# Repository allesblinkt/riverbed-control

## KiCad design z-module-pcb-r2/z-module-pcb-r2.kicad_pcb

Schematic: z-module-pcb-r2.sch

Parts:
C1: 50u; CP_Radial_D7.5mm_P2.50mm
C2, C3, C4, C6, C7: 100n; C_0805
C5, C8: 20p; C_0805
D1: D_Schottky; D_SMA
D2: VacSense; LED_0805
D3: Status; LED_0805
D4: 5V; LED_0805
D5: 24V; LED_0805
D6, D8: BAT_46W; D_SOD-123
D7: Vacuum; LED_0805
D9: Eject; LED_0805
D10, D11, D12, D13, D14, D15, D16, D17, D18, D19, D20, D21, D22, D23, D24, D25, D26, D27, D28, D29: LED; LED_Osram_LW_E67C_LongPads_Thermal
F1: Rihanna; R_1812
F2: Drake; R_1812
HOLE1: 1; MountingHole_3mm
HOLE2: 2; MountingHole_3mm
HOLE3: 3; MountingHole_3mm
HOLE4: 4; MountingHole_3mm
HOLE5, HOLE6, HOLE7, HOLE8, HOLE9, HOLE10, HOLE11, HOLE12: CONN_01X01; MountingHole_2.2mm_M2
HOLE13, HOLE14: CONN_01X01; MountingHole_2.5mm
MB1, MB2, MB3, MB4, MB5, MB6, MB7, MB8, MB9, MB10, MB11, MB12, MB13, MB14, MB15, MB16, MB17, MB18, MB19, MB20: CONN_01X01; Mousebites_5_5mm_0-5mm
P1: Power; Molex_Microfit3_Header_02x02_Straight_43045-0428
P2: X1; RJ45_8-Vertical
P3: X2; RJ45_8-Vertical
P4: ISP; Pin_Header_Straight_2x03_Pitch2.54mm
P5: Z; Molex_Spox_board_4pin
P6: Vacuum; Molex_Microfit3_Header_02x04_Straight_43045-0828
P7: E; Molex_Spox_board_4pin
P8: HomeZ; Molex_Spox_board_3pin
P9: HomeE; Molex_Spox_board_3pin
P10, P18: Light; 0-188275-4_SMD_12-pin_female
P11, P12, P13, P14: 24V; Molex_PicoBlade_53048-0210_02x1.25mm_Angled
P15: 1; Molex_PicoBlade_53047-0210_02x1.25mm_Straight
P16: 2; Molex_PicoBlade_53047-0210_02x1.25mm_Straight
P17: 3; Molex_PicoBlade_53047-0210_02x1.25mm_Straight
P19: 4; Molex_PicoBlade_53047-0210_02x1.25mm_Straight
P20: 5; Molex_PicoBlade_53047-0210_02x1.25mm_Straight
P21: 6; Molex_PicoBlade_53047-0210_02x1.25mm_Straight
Q1, Q2, Q3, Q4, Q5, Q6, Q7, Q8: TSM3404_GSD; SOT-23
R1, R3, R5, R7, R9, R11, R13, R15, R17: 1K; R_0805
R2, R4, R6, R8, R10, R12, R14, R16, R18: *; R_0805
R19, R24, R26, R28, R29, R30, R31, R32, R33: 1K5; R_0805
R20, R21: 300R; R_0805
R22, R25, R27: 2K0; R_0805
R23: 10K; R_0805
R34, R35, R36, R37, R38, R39, R40, R41: 3K3; R_1206
U1: 74HC14; SOIC-14_3.9x8.7mm_Pitch1.27mm
U2, U4, U6: TLP281-4; SOIC-16_3.9x9.9mm_Pitch1.27mm
U3: 7805SR; TO-220
U5: 74HC04; SOIC-14_3.9x8.7mm_Pitch1.27mm
U7: ATMEGA328-AU; TQFP-32_7x7mm_Pitch0.8mm
Y1: Crystal_GND24; Crystal_SMD_3225-4pin_3.2x2.5mm

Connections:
+5V: C2.2, C3.2, C6.2, C7.2, F1.1, P3.8, P4.2, P8.1, P9.1, R1.1, R3.1, R5.1, R7.1, R9.1, R11.1, R13.1, R15.1, R17.1, R21.1, R23.2, U1.14 (VCC), U5.14 (VCC), U7.4 (VCC), U7.6 (VCC), U7.18 (AVCC); also elsewhere on the board
+24V: C1.1, D1.1 (K), D6.1 (K), D7.2 (A), D8.1 (K), D9.2 (A), P6.1, P6.2, P6.3, P10.2, P10.4, P10.6, P10.8, P10.10, P10.12, R22.1, U3.1 (IN); also elsewhere on the board
+28V: P15.1, P16.1, P17.1, P18.2, P18.4, P18.6, P18.8, P18.10, P18.12, P19.1, P20.1, P21.1
/AxisDriver1/M_1A: P5.3; also elsewhere on the board
/AxisDriver1/M_1B: P5.4; also elsewhere on the board
/AxisDriver1/M_2A: P5.2; also elsewhere on the board
/AxisDriver1/M_2B: P5.1; also elsewhere on the board
/AxisDriver2/M_1A: P7.3; also elsewhere on the board
/AxisDriver2/M_1B: P7.4; also elsewhere on the board
/AxisDriver2/M_2A: P7.2; also elsewhere on the board
/AxisDriver2/M_2B: P7.1; also elsewhere on the board
/CONTROL_COMM: P3.4, U4.5, U4.7, U6.1
/E_COMM: P2.8, U2.7, U4.1, U4.3
/E_DIR: U1.4; also elsewhere on the board
/E_DIR_IN: P2.6, R10.1
/E_EN: U1.2; also elsewhere on the board
/E_EN_IN: P2.7, R12.1
/E_HOME_OUT: P3.6, P9.2
/E_STEP: U1.6; also elsewhere on the board
/E_STEP_IN: P2.5, R8.1
/LED_1: P10.1, Q8.3 (D)
/LED_2: P10.3, Q7.3 (D)
/LED_3: P10.5, Q6.3 (D)
/LED_4: P10.7, Q5.3 (D)
/LED_5: P10.9, Q4.3 (D)
/LED_6: P10.11, Q3.3 (D)
/LED_A_A: P11.1, R34.2
/LED_A_K: D14.1 (K), P11.2
/LED_BO_1: P15.2, P18.1
/LED_BO_2: P16.2, P18.3
/LED_BO_3: P17.2, P18.5
/LED_BO_4: P18.7, P19.2
/LED_BO_5: P18.9, P20.2
/LED_BO_6: P18.11, P21.2
/LED_B_A: P12.1, R36.2
/LED_B_K: D19.1 (K), P12.2
/LED_C_A: P13.1, R38.2
/LED_C_K: D24.1 (K), P13.2
/LED_D_A: P14.1, R40.2
/LED_D_K: D29.1 (K), P14.2
/LIGHT_CTRL: U5.6, U7.32 ((PCINT18/INT0)PD2)
/LIGHT_CTRL_IN: P3.3, R18.1
/MISO: P4.1, U7.16 ((PCINT4/MISO)PB4)
/MOSI: P4.4, Q4.1 (G), R29.2, U7.15 ((PCINT3/OC2A/MOSI)PB3)
/PWM_LED_1: Q8.1 (G), R33.1, U7.1 ((PCINT19/OC2B/INT1)PD3)
/PWM_LED_2: Q7.1 (G), R32.1, U7.9 ((PCINT21/OC0B/T1)PD5)
/PWM_LED_3: Q6.1 (G), R31.1, U7.13 ((PCINT1/OC1A)PB1)
/PWM_LED_4: Q5.1 (G), R30.1, U7.14 ((PCINT2/OC1B/~SS~)PB2)
/PWM_LED_6: Q3.1 (G), R28.2, U7.10 ((PCINT22/OC0A/AIN0)PD6)
/RST: C4.2, P4.5, R23.1, U7.29 ((PCINT14/~RESET~)PC6)
/SCK: P4.3, U7.17 ((PCINT5/SCK)PB5)
/STATUSLED_1: R20.1, U7.12 ((PCINT0/CLKO/ICP1)PB0)
/VAC_AUX_AUX: P6.8
/VAC_BLACK_SENSE: D2.2 (A), P6.7
/VAC_BROWN_VAC: D8.2 (A), P6.6, Q2.3 (D), R25.1
/VAC_EJECT: Q1.1 (G), R24.1, U5.4
/VAC_EJECT_IN: P3.2, R16.1
/VAC_ON_IN: P3.1, R14.1
/VAC_SENSE_OUT: P3.7, U6.12
/VAC_VAC: Q2.1 (G), R26.1, U5.2
/VAC_WHITE_EJECT: D6.2 (A), P6.5, Q1.3 (D), R27.1
/XTAL1: C5.1, U7.8 ((PCINT7/XTAL2/TOSC2)PB7), Y1.1
/XTAL2: C8.1, U7.7 ((PCINT6/XTAL1/TOSC1)PB6), Y1.3
/Z_COMM: P2.4, U2.1, U2.3, U2.5
/Z_DIR: U1.10; also elsewhere on the board
/Z_DIR_IN: P2.2, R4.1
/Z_EN: U1.8; also elsewhere on the board
/Z_EN_IN: P2.3, R6.1
/Z_HOME_OUT: P3.5, P8.2
/Z_STEP: U1.12; also elsewhere on the board
/Z_STEP_IN: P2.1, R2.1
GND: C1.2, C2.1, C3.1, C4.1, C5.2, C6.1, C7.1, C8.2, D3.1 (K), D4.1 (K), D5.1 (K), P1.2, P1.4, P2.9, P3.9, P4.6, P6.4, P8.3, P9.3, Q1.2 (S), Q2.2 (S), Q3.2 (S), Q4.2 (S), Q5.2 (S), Q6.2 (S), Q7.2 (S), Q8.2 (S), R24.2, R26.2, R28.1, R29.1, R30.2, R31.2, R32.2, R33.2, U1.7 (GND), U2.9, U2.11, U2.13, U2.15, U3.2 (GND), U4.9, U4.11, U4.13, U4.15, U5.7 (GND), U6.6, U6.11, U6.15, U7.3 (GND), U7.5 (GND), U7.21 (GND), Y1.2, Y1.4; also elsewhere on the board
unnamed: D1.2 (A), F2.1
unnamed: D2.1 (K), R19.1
unnamed: D3.2 (A), R20.2
unnamed: D4.2 (A), R21.2
unnamed: D5.2 (A), R22.2
unnamed: D7.1 (K), R25.2
unnamed: D9.1 (K), R27.2
unnamed: D10.1 (K), D11.2 (A)
unnamed: D10.2 (A), R35.1
unnamed: D11.1 (K), D12.2 (A)
unnamed: D12.1 (K), D13.2 (A)
unnamed: D13.1 (K), D14.2 (A)
unnamed: D15.1 (K), D16.2 (A)
unnamed: D15.2 (A), R37.1
unnamed: D16.1 (K), D17.2 (A)
unnamed: D17.1 (K), D18.2 (A)
unnamed: D18.1 (K), D19.2 (A)
unnamed: D20.1 (K), D21.2 (A)
unnamed: D20.2 (A), R39.1
unnamed: D21.1 (K), D22.2 (A)
unnamed: D22.1 (K), D23.2 (A)
unnamed: D23.1 (K), D24.2 (A)
unnamed: D25.1 (K), D26.2 (A)
unnamed: D25.2 (A), R41.1
unnamed: D26.1 (K), D27.2 (A)
unnamed: D27.1 (K), D28.2 (A)
unnamed: D28.1 (K), D29.2 (A)
unnamed: F1.2, U3.3 (OUT)
unnamed: F2.2, P1.1, P1.3
unnamed: R1.2, U1.13, U2.16
unnamed: R2.2, U2.2
unnamed: R3.2, U1.11, U2.14
unnamed: R4.2, U2.4
unnamed: R5.2, U1.9, U2.12
unnamed: R6.2, U2.6
unnamed: R7.2, U1.5, U2.10
unnamed: R8.2, U2.8
unnamed: R9.2, U1.3, U4.16
unnamed: R10.2, U4.2
unnamed: R11.2, U1.1, U4.14
unnamed: R12.2, U4.4
unnamed: R13.2, U4.12, U5.1
unnamed: R14.2, U4.6
unnamed: R15.2, U4.10, U5.3
unnamed: R16.2, U4.8
unnamed: R17.2, U5.5, U6.16
unnamed: R18.2, U6.2
unnamed: R19.2, U6.5
unnamed: R34.1, R35.2
unnamed: R36.1, R37.2
unnamed: R38.1, R39.2
unnamed: R40.1, R41.2

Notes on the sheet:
Power Input
Status LEDs
Power LEDs
Holes
Motor Drivers
Processor
Switch Inputs
5 V Reg
* = 270 R @ 5V

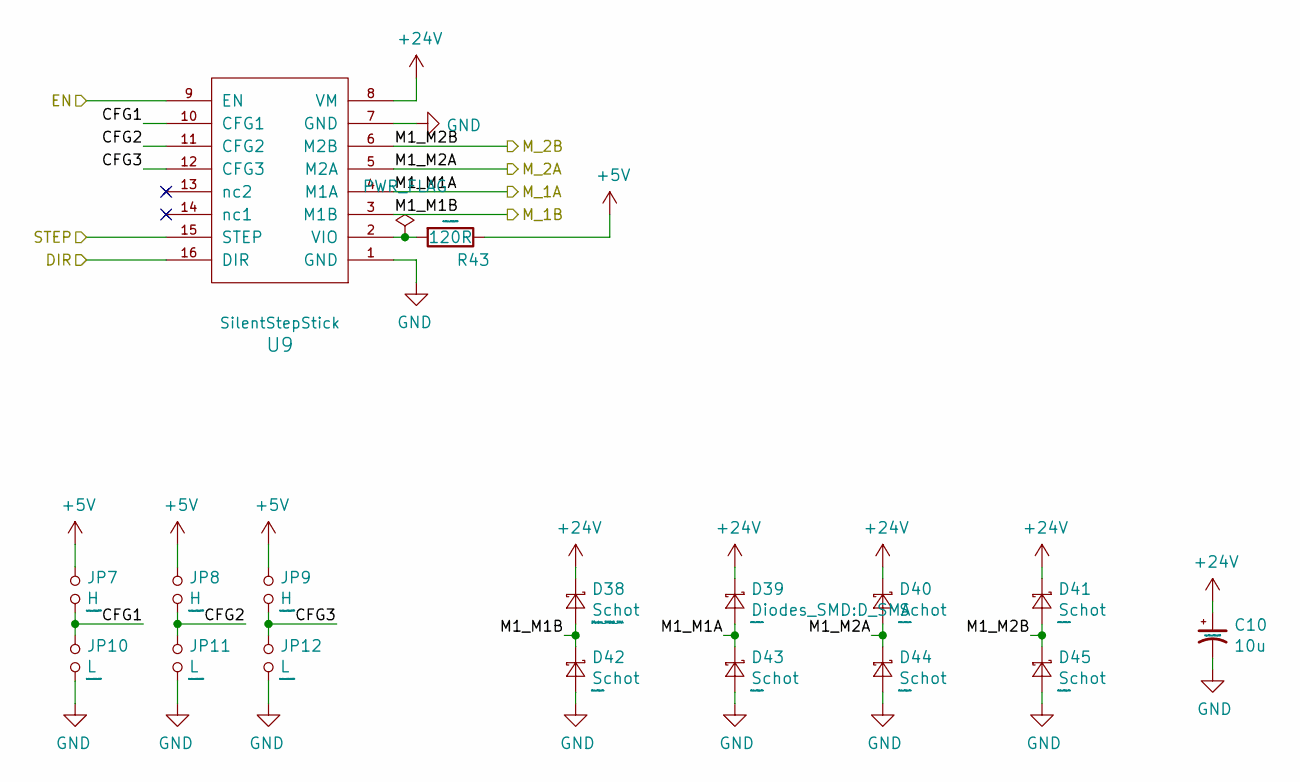
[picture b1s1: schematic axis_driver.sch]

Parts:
C9: 10u; C_1210
D30, D32, D33, D34, D35, D36, D37: Schot; D_SMA
D31: Diodes_SMD:D_SMA; D_SMA
JP1, JP2, JP3: H; R_0805
JP4, JP5, JP6: L; R_0805
R42: 120R; R_0805
U8: SilentStepStick

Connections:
+5V: JP1.1, JP2.1, JP3.1, R42.1; also elsewhere on the board
+24V: C9.1, D30.1 (K), D31.1 (K), D32.1 (K), D33.1 (K), U8.8 (VM); also elsewhere on the board
/AxisDriver2/CFG1: JP1.2, JP4.1, U8.10 (CFG1)
/AxisDriver2/CFG2: JP2.2, JP5.1, U8.11 (CFG2)
/AxisDriver2/CFG3: JP3.2, JP6.1, U8.12 (CFG3)
/AxisDriver2/M_1A: D31.2 (A), D35.1 (K), U8.4 (M1A); also elsewhere on the board
/AxisDriver2/M_1B: D30.2 (A), D34.1 (K), U8.3 (M1B); also elsewhere on the board
/AxisDriver2/M_2A: D32.2 (A), D36.1 (K), U8.5 (M2A); also elsewhere on the board
/AxisDriver2/M_2B: D33.2 (A), D37.1 (K), U8.6 (M2B); also elsewhere on the board
/E_DIR: U8.16 (DIR); also elsewhere on the board
/E_EN: U8.9 (EN); also elsewhere on the board
/E_STEP: U8.15 (STEP); also elsewhere on the board
GND: C9.2, D34.2 (A), D35.2 (A), D36.2 (A), D37.2 (A), JP4.2, JP5.2, JP6.2, U8.1 (GND), U8.7 (GND); also elsewhere on the board
unnamed: R42.2, U8.2 (VIO)

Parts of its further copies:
C10: 10u; C_1210
D38, D40, D41, D42, D43, D44, D45: Schot; D_SMA
D39: Diodes_SMD:D_SMA; D_SMA
JP7, JP8, JP9: H; R_0805
JP10, JP11, JP12: L; R_0805
R43: 120R; R_0805
U9: SilentStepStick

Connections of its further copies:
+5V: JP7.1, JP8.1, JP9.1, R43.1; also elsewhere on the board
+24V: C10.1, D38.1 (K), D39.1 (K), D40.1 (K), D41.1 (K), U9.8 (VM); also elsewhere on the board
/AxisDriver1/CFG1: JP7.2, JP10.1, U9.10 (CFG1)
/AxisDriver1/CFG2: JP8.2, JP11.1, U9.11 (CFG2)
/AxisDriver1/CFG3: JP9.2, JP12.1, U9.12 (CFG3)
/AxisDriver1/M_1A: D39.2 (A), D43.1 (K), U9.4 (M1A); also elsewhere on the board
/AxisDriver1/M_1B: D38.2 (A), D42.1 (K), U9.3 (M1B); also elsewhere on the board
/AxisDriver1/M_2A: D40.2 (A), D44.1 (K), U9.5 (M2A); also elsewhere on the board
/AxisDriver1/M_2B: D41.2 (A), D45.1 (K), U9.6 (M2B); also elsewhere on the board
/Z_DIR: U9.16 (DIR); also elsewhere on the board
/Z_EN: U9.9 (EN); also elsewhere on the board
/Z_STEP: U9.15 (STEP); also elsewhere on the board
GND: C10.2, D42.2 (A), D43.2 (A), D44.2 (A), D45.2 (A), JP10.2, JP11.2, JP12.2, U9.1 (GND), U9.7 (GND); also elsewhere on the board
unnamed: R43.2, U9.2 (VIO)

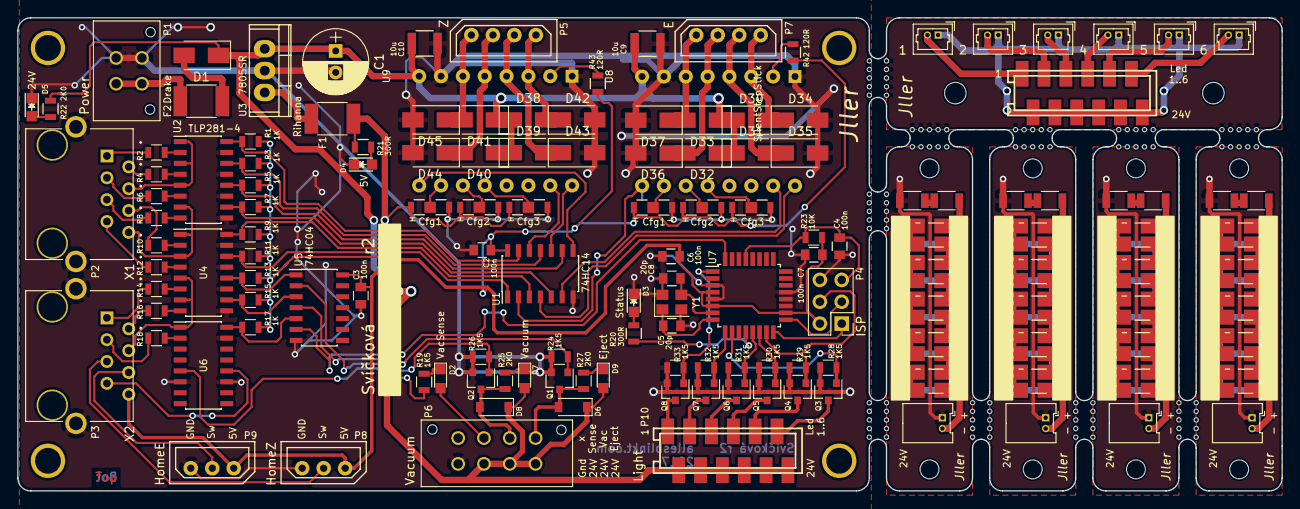
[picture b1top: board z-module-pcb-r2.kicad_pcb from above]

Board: 2 copper layers, 147.0 x 55.0 mm, 185 parts (0 on the bottom side), 131 nets.

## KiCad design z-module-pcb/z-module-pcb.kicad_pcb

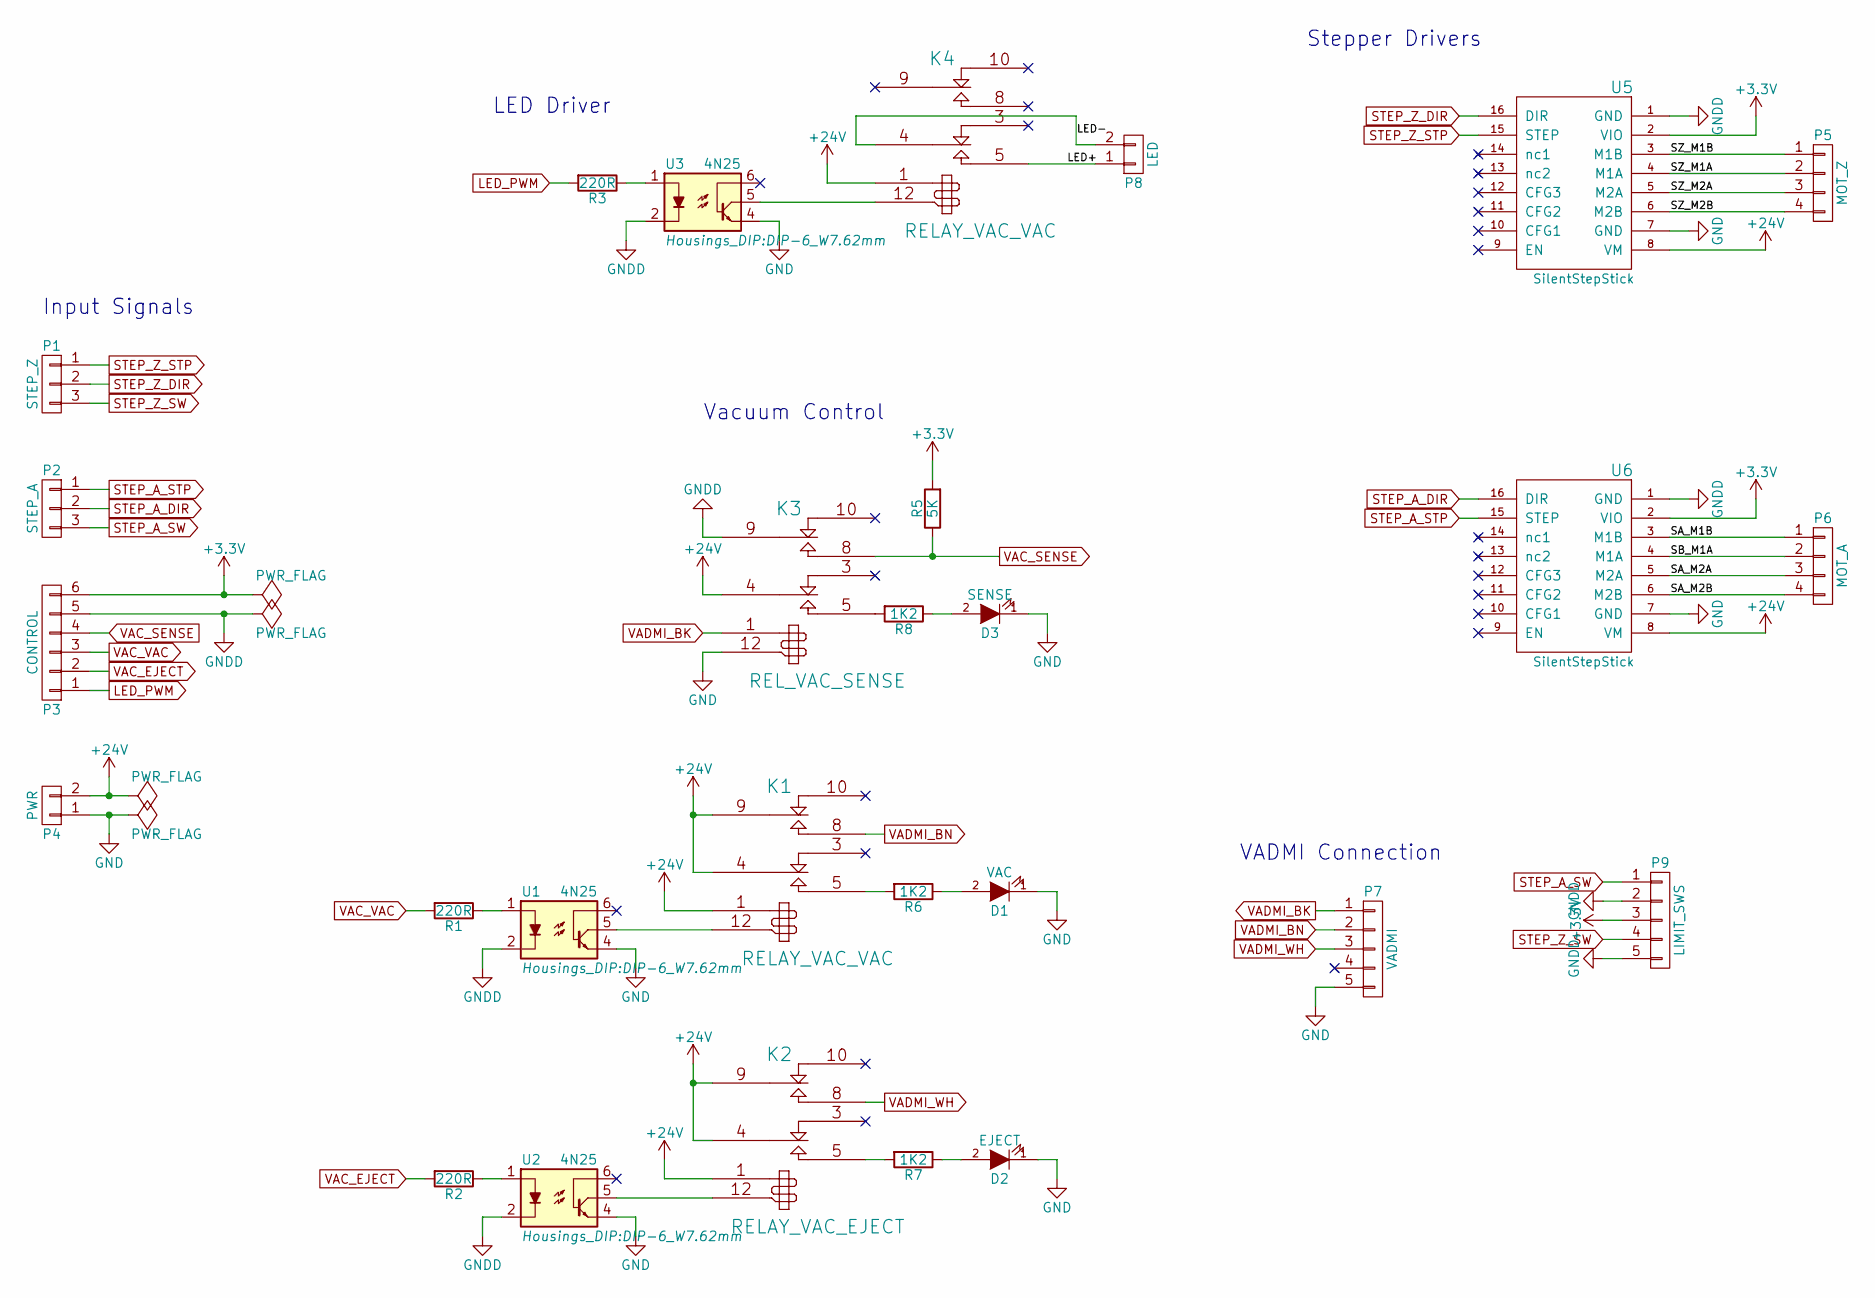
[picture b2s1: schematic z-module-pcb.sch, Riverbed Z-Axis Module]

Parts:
D1: VAC; LED-3MM
D2: EJECT; LED-3MM
D3: SENSE; LED-3MM
K1, K4: RELAY_VAC_VAC; AxicomRelay-V23079
K2: RELAY_VAC_EJECT; AxicomRelay-V23079
K3: REL_VAC_SENSE; AxicomRelay-V23079
P1: STEP_Z; AKL_182-03
P2: STEP_A; AKL_182-03
P3: CONTROL; AKL_182-06
P4: PWR; AKL_182-02
P5: MOT_Z; AKL_182-04
P6: MOT_A; AKL_182-04
P7: VADMI; AKL_182-05
P8: LED; AKL_182-02
P9: LIMIT_SWS; AKL_182-05
R1, R2, R3: 220R; Resistor_Horizontal_RM10mm
R5: 5K; Resistor_Horizontal_RM10mm
R6, R7, R8: 1K2; Resistor_Horizontal_RM10mm
U1, U2, U3: 4N25; DIP-6_W7.62mm
U5, U6: SilentStepStick

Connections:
+3V3: P3.6, P9.3, R5.2, U5.2 (VIO), U6.2 (VIO)
+24V: K1.1, K1.4, K1.9, K2.1, K2.4, K2.9, K3.4, K4.1, P4.2, U5.8 (VM), U6.8 (VM)
/LED+: K4.5, P8.1
/LED-: K4.4, P8.2
/SA_M1B: P6.1, U6.3 (M1B)
/SA_M2A: P6.3, U6.5 (M2A)
/SA_M2B: P6.4, U6.6 (M2B)
/SB_M1A: P6.2, U6.4 (M1A)
/SZ_M1A: P5.2, U5.4 (M1A)
/SZ_M1B: P5.1, U5.3 (M1B)
/SZ_M2A: P5.3, U5.5 (M2A)
/SZ_M2B: P5.4, U5.6 (M2B)
GND: D1.1 (K), D2.1 (K), D3.1 (K), K3.12, P4.1, P7.5, U1.4, U2.4, U3.4, U5.7 (GND), U6.7 (GND)
GNDD: K3.9, P3.5, P9.2, P9.5, U1.2, U2.2, U3.2, U5.1 (GND), U6.1 (GND)
LED_PWM: P3.1, R3.2
unnamed: D1.2 (A), R6.1
unnamed: D2.2 (A), R7.1
unnamed: D3.2 (A), R8.1
unnamed: K1.5, R6.2
unnamed: K1.12, U1.5
unnamed: K2.5, R7.2
unnamed: K2.12, U2.5
unnamed: K3.5, R8.2
unnamed: K4.12, U3.5
unnamed: R1.1, U1.1
unnamed: R2.1, U2.1
unnamed: R3.1, U3.1
STEP_A_DIR: P2.2, U6.16 (DIR)
STEP_A_STP: P2.1, U6.15 (STEP)
STEP_A_SW: P2.3, P9.1
STEP_Z_DIR: P1.2, U5.16 (DIR)
STEP_Z_STP: P1.1, U5.15 (STEP)
STEP_Z_SW: P1.3, P9.4
VAC_EJECT: P3.2, R2.2
VAC_SENSE: K3.8, P3.4, R5.1
VAC_VAC: P3.3, R1.2
VADMI_BK: K3.1, P7.1
VADMI_BN: K1.8, P7.2
VADMI_WH: K2.8, P7.3

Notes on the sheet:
Stepper Drivers
VADMI Connection
LED Driver
Vacuum Control
Input Signals

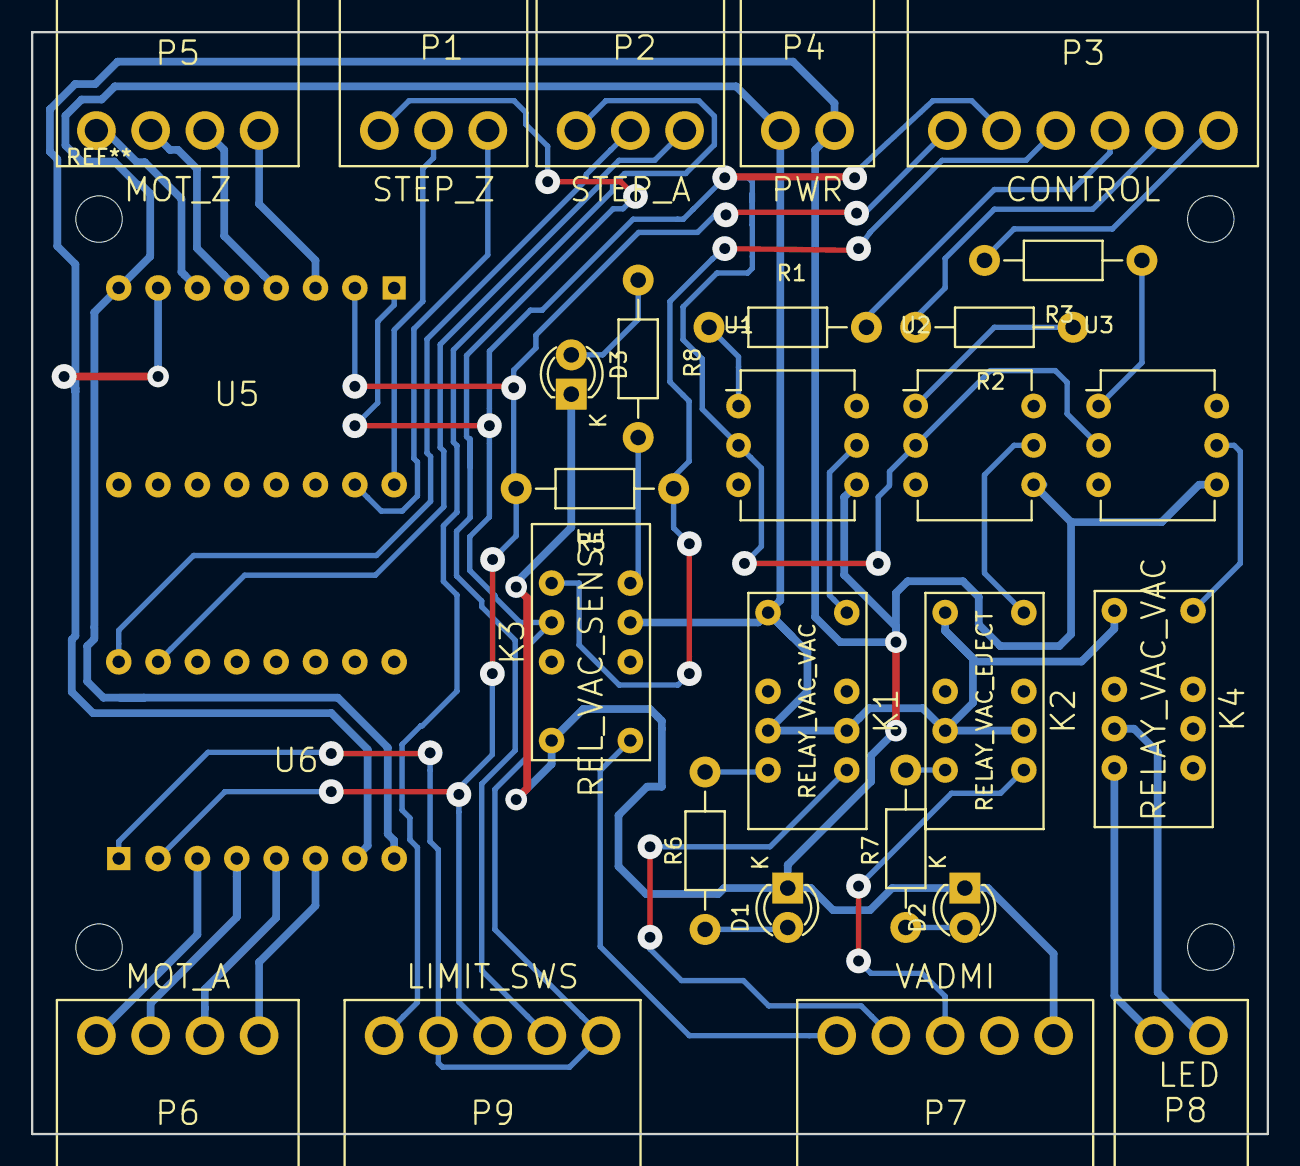
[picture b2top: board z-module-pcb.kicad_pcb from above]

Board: 2 copper layers, 79.8 x 71.1 mm, 28 parts (0 on the bottom side), 39 nets.

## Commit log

2015-11-08 Readme
2015-11-08 Added gitignore
2015-11-09 Added notes for signals of Z-Axis
2015-11-09 Relay thoughts
2015-11-09 Ignoring some Kicad files
2015-11-09 Signal definitions
2015-11-09 PCB schematic and layout WiP. Libraries with custom components.
2015-11-10 Layout almost done. To be checked.
2015-11-10 Schematic PDF
2015-11-14 Finalized and cleaned design
2015-11-14 Fabrication files
2015-11-22 Added pinouts
2015-11-22 Added notes and first config
2015-11-22 Added wiring thoughts
2015-11-23 Deleted Smoothie config, because moved to riverbed-vision.git
2017-08-10 Added footprints for new head board
2017-08-10 Added libs
2017-08-10 Added final project files for new head board
2017-08-10 Added fab files as sent to elecrow
